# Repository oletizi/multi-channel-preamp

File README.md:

# Multi-Channel Preamp

## Description
Currently experimental KiCAD-based PCB project for a multi-channel vacuum tube preamp with insertable EQ.

## Layout
* `/src` where all the stuff is.
* `/src/schematics` where the KiCAD files live.
* `/src/schematics/build` where the KiCAD output files go. These are not under VC.
* `/src/schematics/610-output` example schematic from UA 610 preamp.
* `/src/gyraf-output` example preamp output stage from gyraf suitable for driving output transformer.
* `/src/multi-channel-preamp` schematics for the actual preamp.
* `/src/pmillett-output` example tube mic preamp schematic from pmillett.
* `/src/pultec-boost-high` prototype schematic & PCB for pultec-style high boost (from [Ian Thompson-Bell's Pultec 3 Band EQ](https://drive.google.com/drive/folders/0B_n67A1hN3qtfnhqS002NUo2WF9OTkZONDNqc3RBTS05SFlWLU4tbWItYVlZc01zejdrbGM?resourcekey=0-kD50Ger3JRaC0WO6iRfwKg)).
* `/src/pultec-cut-high` prototype schematic & PCB for pultec-style high cut (from [Ian Thompson-Bell's Pultec 3 Band EQ](https://drive.google.com/drive/folders/0B_n67A1hN3qtfnhqS002NUo2WF9OTkZONDNqc3RBTS05SFlWLU4tbWItYVlZc01zejdrbGM?resourcekey=0-kD50Ger3JRaC0WO6iRfwKg))
* `/src/pultec-three-band-eq` prototype schematic & PCB for full pultec-style 3-band eq (from [Ian Thompson-Bell's Pultec 3 Band EQ](https://drive.google.com/drive/folders/0B_n67A1hN3qtfnhqS002NUo2WF9OTkZONDNqc3RBTS05SFlWLU4tbWItYVlZc01zejdrbGM?resourcekey=0-kD50Ger3JRaC0WO6iRfwKg))

* `tapeop-output` example tube mic preamp schematic from TapeOp.

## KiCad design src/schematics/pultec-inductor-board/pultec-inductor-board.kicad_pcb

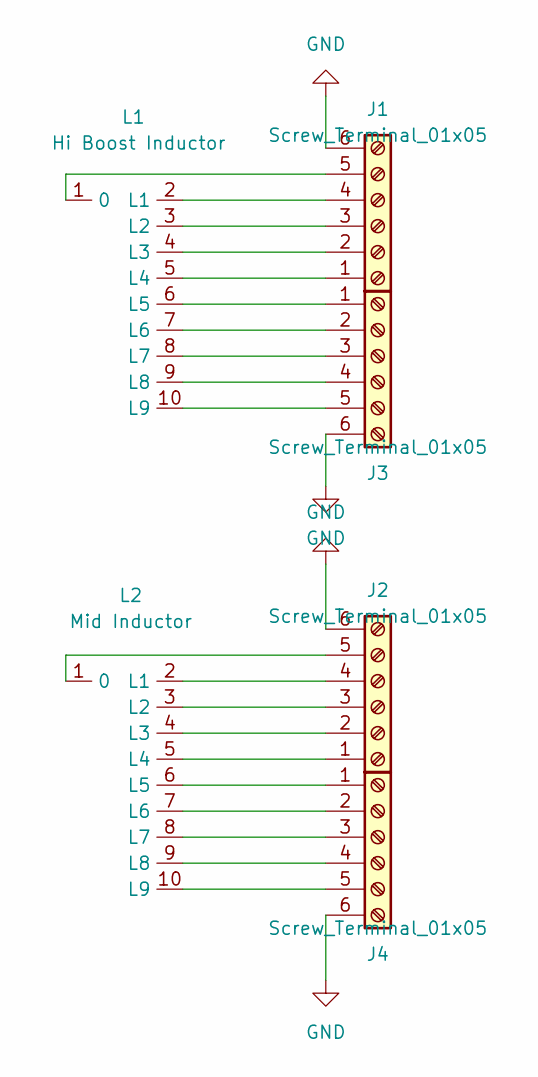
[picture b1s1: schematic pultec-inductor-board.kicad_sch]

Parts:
J1, J2, J3, J4: Screw_Terminal_01x05; TerminalBlock_Phoenix_MKDS-1,5-6_1x06_P5.00mm_Horizontal_Fa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
L1: Hi Boost Inductor; multi-inductor_EE16_10pin
L2: Mid Inductor; multi-inductor_EE16_10pin

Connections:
GND: J1.6, J2.6, J3.6, J4.6
unnamed: J1.1, L1.5 (L4)
unnamed: J1.2, L1.4 (L3)
unnamed: J1.3, L1.3 (L2)
unnamed: J1.4, L1.2 (L1)
unnamed: J1.5, L1.1 (0)
unnamed: J2.1, L2.5 (L4)
unnamed: J2.2, L2.4 (L3)
unnamed: J2.3, L2.3 (L2)
unnamed: J2.4, L2.2 (L1)
unnamed: J2.5, L2.1 (0)
unnamed: J3.1, L1.6 (L5)
unnamed: J3.2, L1.7 (L6)
unnamed: J3.3, L1.8 (L7)
unnamed: J3.4, L1.9 (L8)
unnamed: J3.5, L1.10 (L9)
unnamed: J4.1, L2.6 (L5)
unnamed: J4.2, L2.7 (L6)
unnamed: J4.3, L2.8 (L7)
unnamed: J4.4, L2.9 (L8)
unnamed: J4.5, L2.10 (L9)

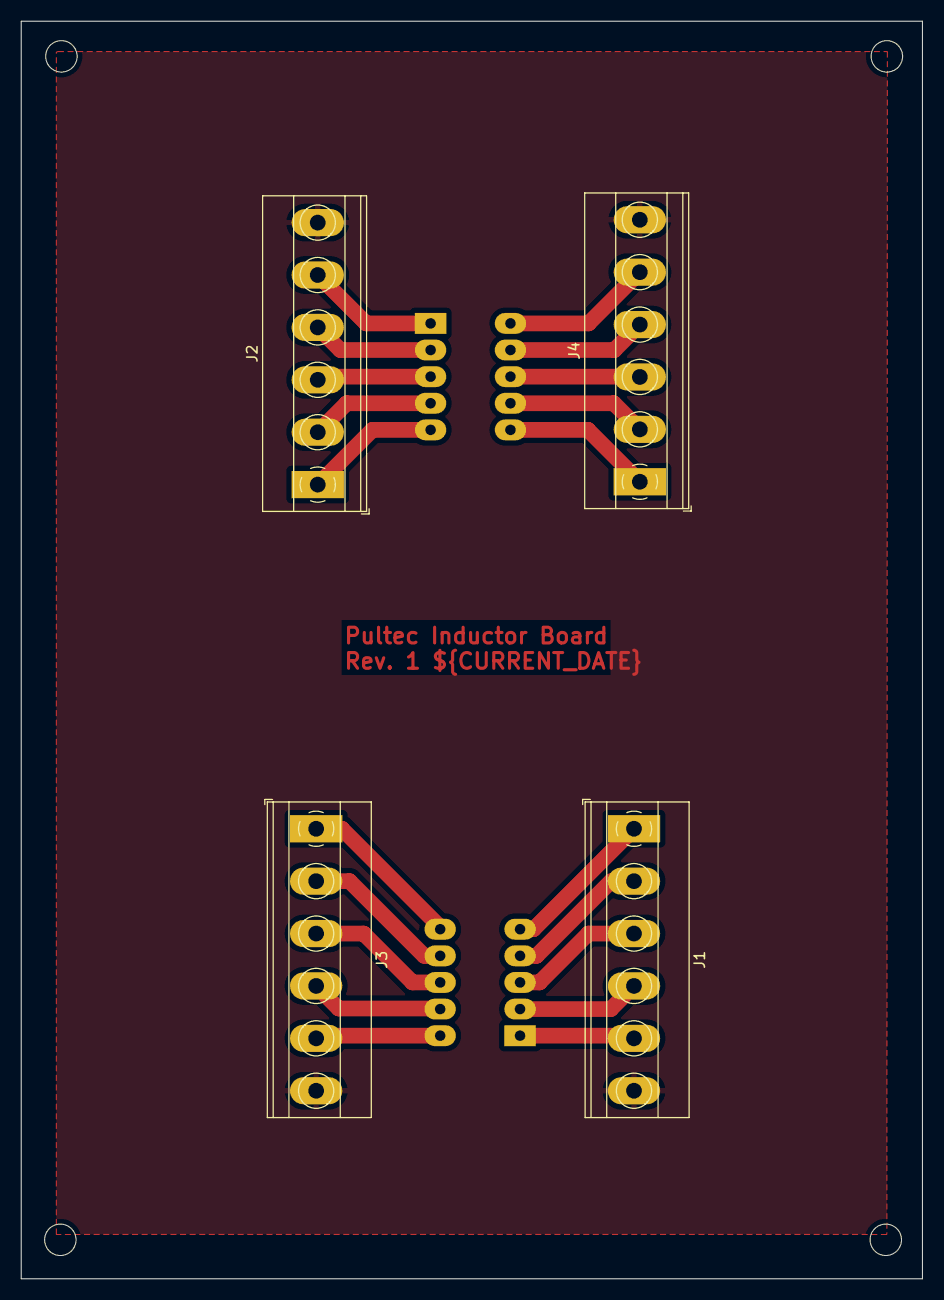
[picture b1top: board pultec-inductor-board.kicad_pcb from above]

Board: 2 copper layers, 86.0 x 120.0 mm, 6 parts (0 on the bottom side), 21 nets.

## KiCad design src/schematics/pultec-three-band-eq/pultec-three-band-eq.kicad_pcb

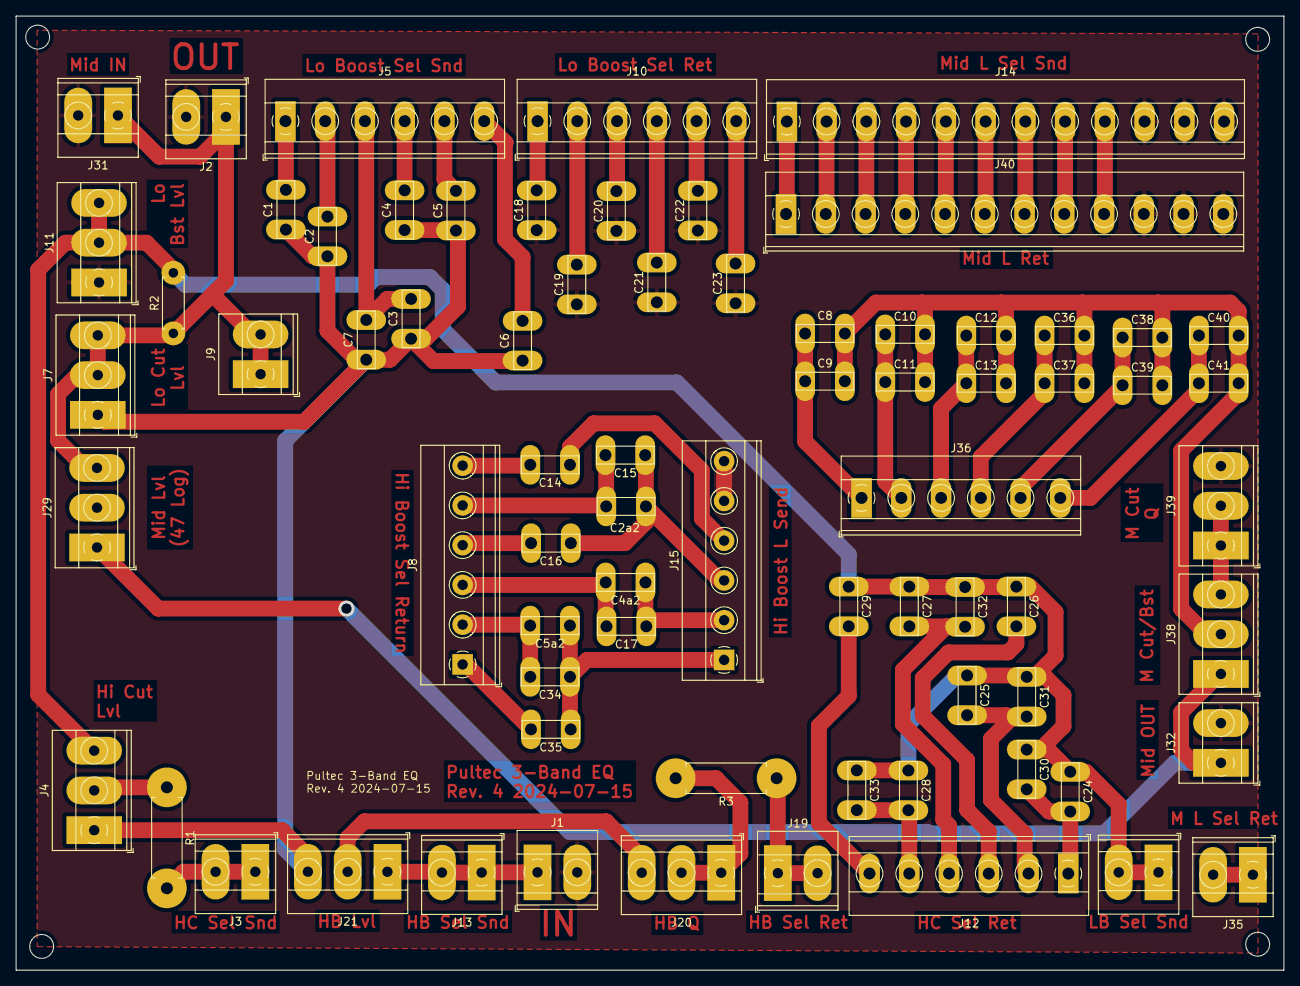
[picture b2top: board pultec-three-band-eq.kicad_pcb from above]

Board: 2 copper layers, 159.5 x 120.0 mm, 73 parts (0 on the bottom side), 57 nets.

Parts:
C1: 18n; C_Rect_L7.0mm_W2.0mm_P5.00mm_Fat_Pad
C2, C31, C32: 10n; C_Rect_L7.0mm_W2.0mm_P5.00mm_Fat_Pad
C2a2: 470pF; C_Rect_L7.0mm_W2.0mm_P5.00mm_Fat_Pad
C3: 4.7n; C_Rect_L7.0mm_W2.0mm_P5.00mm_Fat_Pad
C4, C16: 3n3; C_Rect_L7.0mm_W2.0mm_P5.00mm_Fat_Pad
C4a2, C17, C34, C35: 1nF; C_Rect_L7.0mm_W2.0mm_P5.00mm_Fat_Pad
C5, C33: 2n2; C_Rect_L7.0mm_W2.0mm_P5.00mm_Fat_Pad
C5a2: 1n5; C_Rect_L7.0mm_W2.0mm_P5.00mm_Fat_Pad
C6: 1n8; C_Rect_L7.0mm_W2.0mm_P5.00mm_Fat_Pad
C7: 1n; C_Rect_L7.0mm_W2.0mm_P5.00mm_Fat_Pad
C8: Mid C1A; C_Rect_L7.0mm_W2.0mm_P5.00mm_Fat_Pad
C9: Mid C1B; C_Rect_L7.0mm_W2.0mm_P5.00mm_Fat_Pad
C10: Mid C2A; C_Rect_L7.0mm_W2.0mm_P5.00mm_Fat_Pad
C11: Mid C2B; C_Rect_L7.0mm_W2.0mm_P5.00mm_Fat_Pad
C12: Mid C3A; C_Rect_L7.0mm_W2.0mm_P5.00mm_Fat_Pad
C13: Mid C3B; C_Rect_L7.0mm_W2.0mm_P5.00mm_Fat_Pad
C14, C15: 4n7; C_Rect_L7.0mm_W2.0mm_P5.00mm_Fat_Pad
C18: 330n; C_Rect_L7.0mm_W2.0mm_P5.00mm_Fat_Pad
C19: 220n; C_Rect_L7.0mm_W2.0mm_P5.00mm_Fat_Pad
C20: 120n; C_Rect_L7.0mm_W2.0mm_P5.00mm_Fat_Pad
C21: 68n; C_Rect_L7.0mm_W2.0mm_P5.00mm_Fat_Pad
C22, C24, C25, C26: 47n; C_Rect_L7.0mm_W2.0mm_P5.00mm_Fat_Pad
C23, C30: 33n; C_Rect_L7.0mm_W2.0mm_P5.00mm_Fat_Pad
C27, C28: 22n; C_Rect_L7.0mm_W2.0mm_P5.00mm_Fat_Pad
C29: 15n; C_Rect_L7.0mm_W2.0mm_P5.00mm_Fat_Pad
C36: Mid C4A; C_Rect_L7.0mm_W2.0mm_P5.00mm_Fat_Pad
C37: Mid C4B; C_Rect_L7.0mm_W2.0mm_P5.00mm_Fat_Pad
C38: Mid C5A; C_Rect_L7.0mm_W2.0mm_P5.00mm_Fat_Pad
C39: Mid C5B; C_Rect_L7.0mm_W2.0mm_P5.00mm_Fat_Pad
C40: Mid C6A; C_Rect_L7.0mm_W2.0mm_P5.00mm_Fat_Pad
C41: Mid C6B; C_Rect_L7.0mm_W2.0mm_P5.00mm_Fat_Pad
J1: IN; TerminalBlock_Phoenix_MKDS-1,5-2_1x02_P5.00mm_Horizontal Fa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
J2: OUT; TerminalBlock_Phoenix_MKDS-1,5-2_1x02_P5.00mm_Horizontal Fa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
J3: Hi Cut Sel Snd; TerminalBlock_Phoenix_MKDS-1,5-2_1x02_P5.00mm_Horizontal Fa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
J4: Hi Cut Lvl; TerminalBlock_Phoenix_MKDS-1,5-3_1x03_P5.00mm_Horizontal Fa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
J5: Lo Cut Sel Snd; TerminalBlock_Phoenix_MKDS-1,5-6_1x06_P5.00mm_Horizontal_Fa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
J6: Lo Boost Sel Snd; TerminalBlock_Phoenix_MKDS-1,5-2_1x02_P5.00mm_Horizontal Fa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
J7: Low Cut Lvl; TerminalBlock_Phoenix_MKDS-1,5-3_1x03_P5.00mm_Horizontal Fa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
J8: Hi Boost Sel Rtn; TerminalBlock_Phoenix_MKDS-1,5-6_1x06_P5.00mm_Horizontal
J9: Low Cut Sel Ret; TerminalBlock_Phoenix_MKDS-1,5-2_1x02_P5.00mm_Horizontal Fa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
J10: Lo Boost Sel Ret; TerminalBlock_Phoenix_MKDS-1,5-6_1x06_P5.00mm_Horizontal_Fa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
J11: Lo Boost Lvl; TerminalBlock_Phoenix_MKDS-1,5-3_1x03_P5.00mm_Horizontal Fa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
J12: Hi Cut Sel Ret; TerminalBlock_Phoenix_MKDS-1,5-6_1x06_P5.00mm_Horizontal_Fa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
J13: Hi Boost Sel Snd; TerminalBlock_Phoenix_MKDS-1,5-2_1x02_P5.00mm_Horizontal Fa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
J14: Mid L Sel send; TerminalBlock_Phoenix_MKDS-1,5-12_1x12_P5.00mm_Horizontal_F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
J15: Hi Boost L Snd; TerminalBlock_Phoenix_MKDS-1,5-6_1x06_P5.00mm_Horizontal
J19: Hi Boost Sel Ret; TerminalBlock_Phoenix_MKDS-1,5-2_1x02_P5.00mm_Horizontal Fa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
J20: Hi Boost Q; TerminalBlock_Phoenix_MKDS-1,5-3_1x03_P5.00mm_Horizontal Fa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
J21: Hi Boost Lvl; TerminalBlock_Phoenix_MKDS-1,5-3_1x03_P5.00mm_Horizontal Fa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
J29: Mid Lvl (47 Log); TerminalBlock_Phoenix_MKDS-1,5-3_1x03_P5.00mm_Horizontal Fa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
J31: Mid In; TerminalBlock_Phoenix_MKDS-1,5-2_1x02_P5.00mm_Horizontal Fa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
J32: Mid Out; TerminalBlock_Phoenix_MKDS-1,5-2_1x02_P5.00mm_Horizontal Fa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
J35: Mid L Sel Ret/C Sel Snd; TerminalBlock_Phoenix_MKDS-1,5-2_1x02_P5.00mm_Horizontal Fa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
J36: Mid C Sel Ret; TerminalBlock_Phoenix_MKDS-1,5-6_1x06_P5.00mm_Horizontal_Fa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
J38: Mid Cut/Bst Sw; TerminalBlock_Phoenix_MKDS-1,5-3_1x03_P5.00mm_Horizontal Fa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
J39: Mid Cut Q; TerminalBlock_Phoenix_MKDS-1,5-3_1x03_P5.00mm_Horizontal Fa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
J40: Mid L Ret; TerminalBlock_Phoenix_MKDS-1,5-12_1x12_P5.00mm_Horizontal_F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
R1: 430R; R_Axial_DIN0411_L9.9mm_D3.6mm_P12.70mm_Horizontal Fat Pad
R2: 56K; R_Axial_DIN0207_L6.3mm_D2.5mm_P7.62mm_Horizontal
R3: 4K7; R_Axial_DIN0411_L9.9mm_D3.6mm_P12.70mm_Horizontal Fat Pad

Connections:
/HI BOOST OUT: C1.1, C2.1, C3.1, C4.1, C5.1, C6.1, C7.1, J4.1, J7.1, J21.3
/IN: J1.1, J13.1, J13.2, J21.1
/LO BOOST IN: C24.1, C25.1, C26.1, C27.1, C28.1, C29.1, C30.1, C31.1, C32.1, C33.1, J4.3, J6.1, J6.2, J11.2, J11.3, R2.2
/OUT: J2.1, J7.2, J7.3, J9.1, J9.2, J29.3, J31.1, R2.1
/pultec-mid-band/MID OUT: J29.1, J32.1, J38.1
GND: C18.1, C19.1, C20.1, C21.1, C22.1, C23.1, J1.2, J2.2, J11.1, J14.10, J14.11, J14.12, J15.5, J15.6, J31.2, J32.2, J39.3, J40.10, J40.11, J40.12
unnamed: J3.1, J3.2, R1.2
unnamed: J4.2, R1.1
unnamed: C1.2, J5.1
unnamed: C2.2, J5.2
unnamed: C3.2, C7.2, J5.3
unnamed: C4.2, J5.4
unnamed: C5.2, J5.5
unnamed: C6.2, J5.6
unnamed: C35.2, J8.1
unnamed: C5a2.2, C34.2, J8.2
unnamed: C4a2.2, C17.2, J8.3
unnamed: C16.2, J8.4
unnamed: C2a2.2, C15.2, J8.5
unnamed: C14.2, J8.6
unnamed: C18.2, J10.1
unnamed: C19.2, J10.2
unnamed: C20.2, J10.3
unnamed: C21.2, J10.4
unnamed: C22.2, J10.5
unnamed: C23.2, J10.6
unnamed: C24.2, C30.2, J12.1
unnamed: C25.2, C31.2, J12.2
unnamed: C26.2, J12.3
unnamed: C27.2, C32.2, J12.4
unnamed: C28.2, C33.2, J12.5
unnamed: C29.2, J12.6
unnamed: J14.1, J40.1
unnamed: J14.2, J40.2
unnamed: J14.3, J40.3
unnamed: J14.4, J40.4
unnamed: J14.5, J40.5
unnamed: J14.6, J40.6
unnamed: J14.7, J40.7
unnamed: J14.8, J40.8
unnamed: J14.9, J40.9
unnamed: C5a2.1, C34.1, C35.1, J15.1
unnamed: C4a2.1, C17.1, J15.2
unnamed: C2a2.1, C15.1, C16.1, J15.3
unnamed: C14.1, J15.4
unnamed: J19.1, J19.2, R3.1
unnamed: J20.1, J20.2, R3.2
unnamed: J20.3, J21.2
unnamed: J35.1, J35.2
unnamed: C8.1, C9.1, J36.1
unnamed: C10.1, C11.1, J36.2
unnamed: C12.1, C13.1, J36.3
unnamed: C36.1, C37.1, J36.4
unnamed: C38.1, C39.1, J36.5
unnamed: C40.1, C41.1, J36.6
unnamed: C8.2, C9.2, C10.2, C11.2, C12.2, C13.2, C36.2, C37.2, C38.2, C39.2, C40.2, C41.2, J38.2
unnamed: J38.3, J39.1, J39.2

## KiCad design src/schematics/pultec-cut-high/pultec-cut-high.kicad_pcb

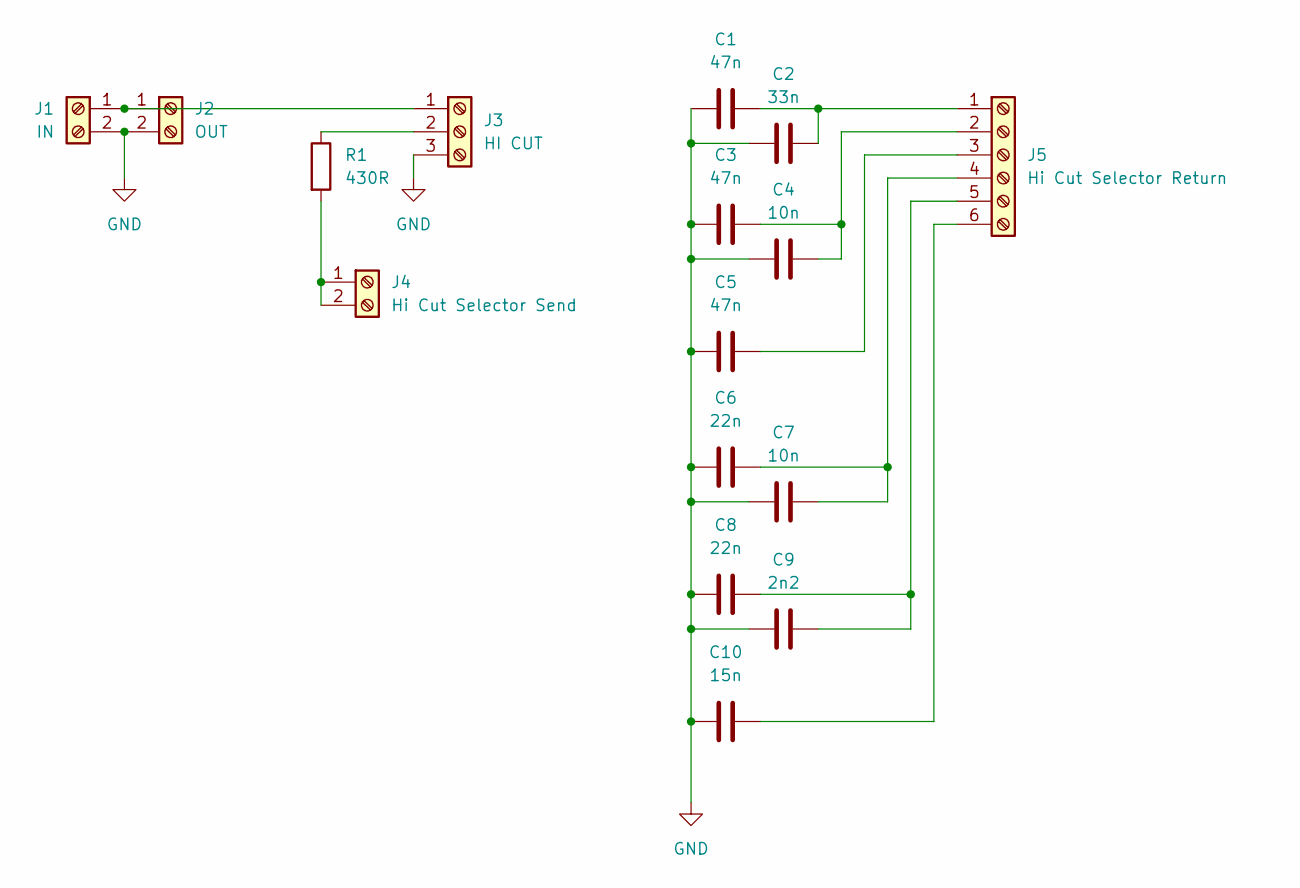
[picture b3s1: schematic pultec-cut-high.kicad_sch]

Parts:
C1, C3, C5: 47n; C_Rect_L7.0mm_W2.0mm_P5.00mm_Fat_Pad
C2: 33n; C_Rect_L7.0mm_W2.0mm_P5.00mm_Fat_Pad
C4, C7: 10n; C_Rect_L7.0mm_W2.0mm_P5.00mm_Fat_Pad
C6, C8: 22n; C_Rect_L7.0mm_W2.0mm_P5.00mm_Fat_Pad
C9: 2n2; C_Rect_L7.0mm_W2.0mm_P5.00mm_Fat_Pad
C10: 15n; C_Rect_L7.0mm_W2.0mm_P5.00mm_Fat_Pad
J1: IN; TerminalBlock_Phoenix_MKDS-1,5-2_1x02_P5.00mm_Horizontal Fa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
J2: OUT; TerminalBlock_Phoenix_MKDS-1,5-2_1x02_P5.00mm_Horizontal Fa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
J3: HI CUT; TerminalBlock_Phoenix_MKDS-1,5-3_1x03_P5.00mm_Horizontal Fa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
J4: Hi Cut Selector Send; TerminalBlock_Phoenix_MKDS-1,5-2_1x02_P5.00mm_Horizontal Fa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
J5: Hi Cut Selector Return; TerminalBlock_Phoenix_MKDS-1,5-6_1x06_P5.00mm_Horizontal_Fa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
R1: 430R; R_Axial_DIN0411_L9.9mm_D3.6mm_P12.70mm_Horizontal Fat Pad

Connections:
GND: C1.1, C2.1, C3.1, C4.1, C5.1, C6.1, C7.1, C8.1, C9.1, C10.1, J1.2, J2.2, J3.3
unnamed: J1.1, J2.1, J3.1
unnamed: J3.2, R1.1
unnamed: J4.1, J4.2, R1.2
unnamed: C1.2, C2.2, J5.1
unnamed: C3.2, C4.2, J5.2
unnamed: C5.2, J5.3
unnamed: C6.2, C7.2, J5.4
unnamed: C8.2, C9.2, J5.5
unnamed: C10.2, J5.6

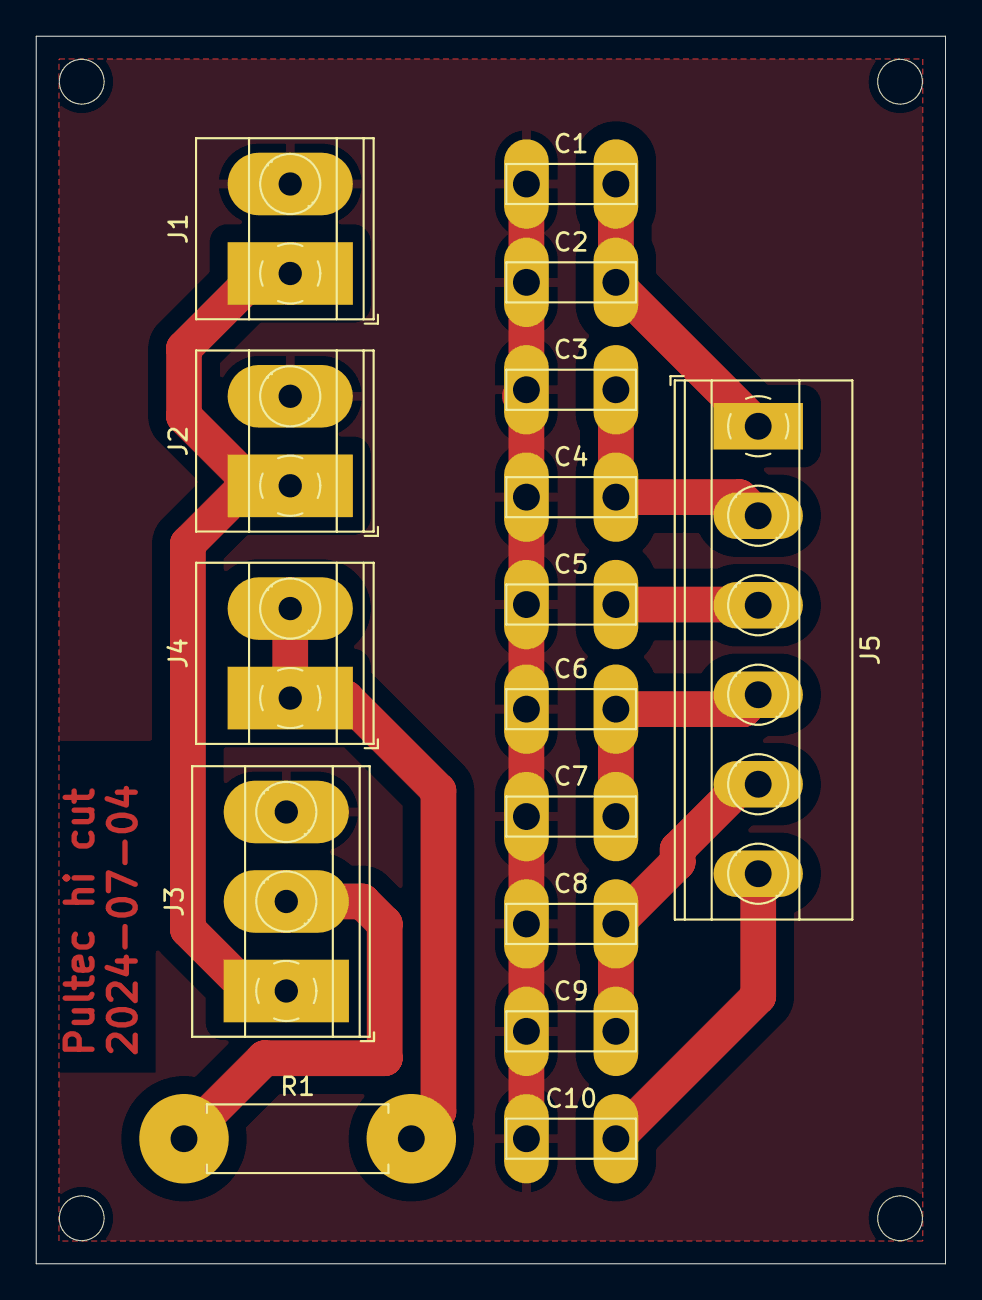
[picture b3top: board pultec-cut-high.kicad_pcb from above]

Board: 2 copper layers, 50.8 x 68.6 mm, 16 parts (0 on the bottom side), 10 nets.

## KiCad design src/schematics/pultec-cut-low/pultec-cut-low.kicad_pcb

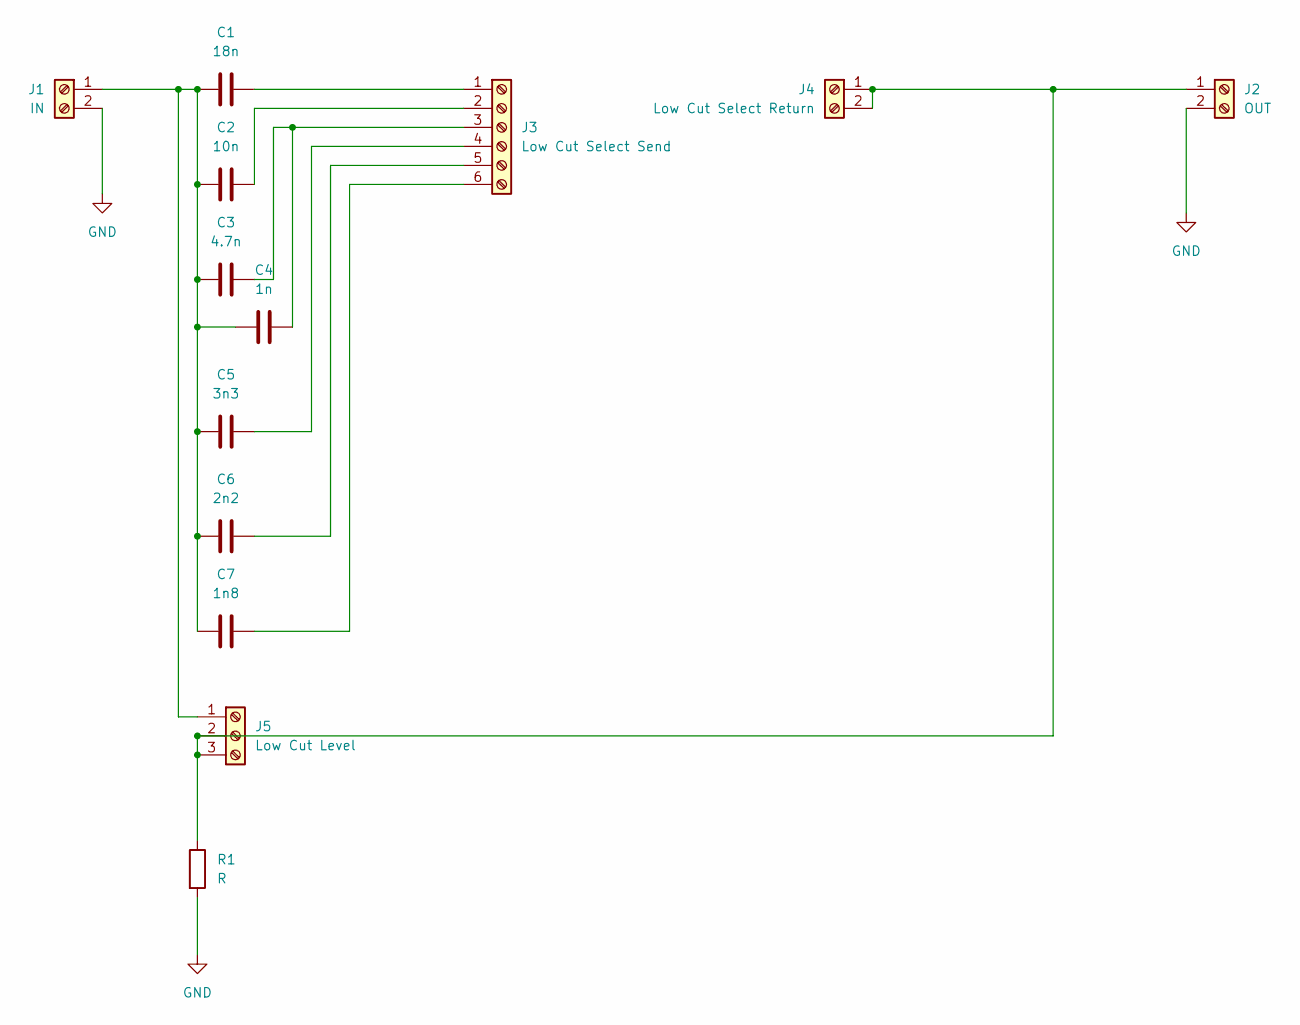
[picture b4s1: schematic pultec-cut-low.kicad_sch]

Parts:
C1: 18n; C_Rect_L7.0mm_W2.0mm_P5.00mm_Fat_Pad
C2: 10n; C_Rect_L7.0mm_W2.0mm_P5.00mm_Fat_Pad
C3: 4.7n; C_Rect_L7.0mm_W2.0mm_P5.00mm_Fat_Pad
C4: 1n; C_Rect_L7.0mm_W2.0mm_P5.00mm_Fat_Pad
C5: 3n3; C_Rect_L7.0mm_W2.0mm_P5.00mm_Fat_Pad
C6: 2n2; C_Rect_L7.0mm_W2.0mm_P5.00mm_Fat_Pad
C7: 1n8; C_Rect_L7.0mm_W2.0mm_P5.00mm_Fat_Pad
J1: IN; TerminalBlock_Phoenix_MKDS-1,5-2_1x02_P5.00mm_Horizontal Fa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
J2: OUT; TerminalBlock_Phoenix_MKDS-1,5-2_1x02_P5.00mm_Horizontal Fa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
J3: Low Cut Select Send; TerminalBlock_Phoenix_MKDS-1,5-6_1x06_P5.00mm_Horizontal_Fa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
J4: Low Cut Select Return; TerminalBlock_Phoenix_MKDS-1,5-2_1x02_P5.00mm_Horizontal Fa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
J5: Low Cut Level; TerminalBlock_Phoenix_MKDS-1,5-3_1x03_P5.00mm_Horizontal Fa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
R1: R; R_Axial_DIN0207_L6.3mm_D2.5mm_P7.62mm_Horizontal

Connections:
GND: J1.2, J2.2, R1.2
unnamed: C1.1, C2.1, C3.1, C4.1, C5.1, C6.1, C7.1, J1.1, J5.1
unnamed: J2.1, J4.1, J4.2, J5.2, J5.3, R1.1
unnamed: C1.2, J3.1
unnamed: C2.2, J3.2
unnamed: C3.2, C4.2, J3.3
unnamed: C5.2, J3.4
unnamed: C6.2, J3.5
unnamed: C7.2, J3.6

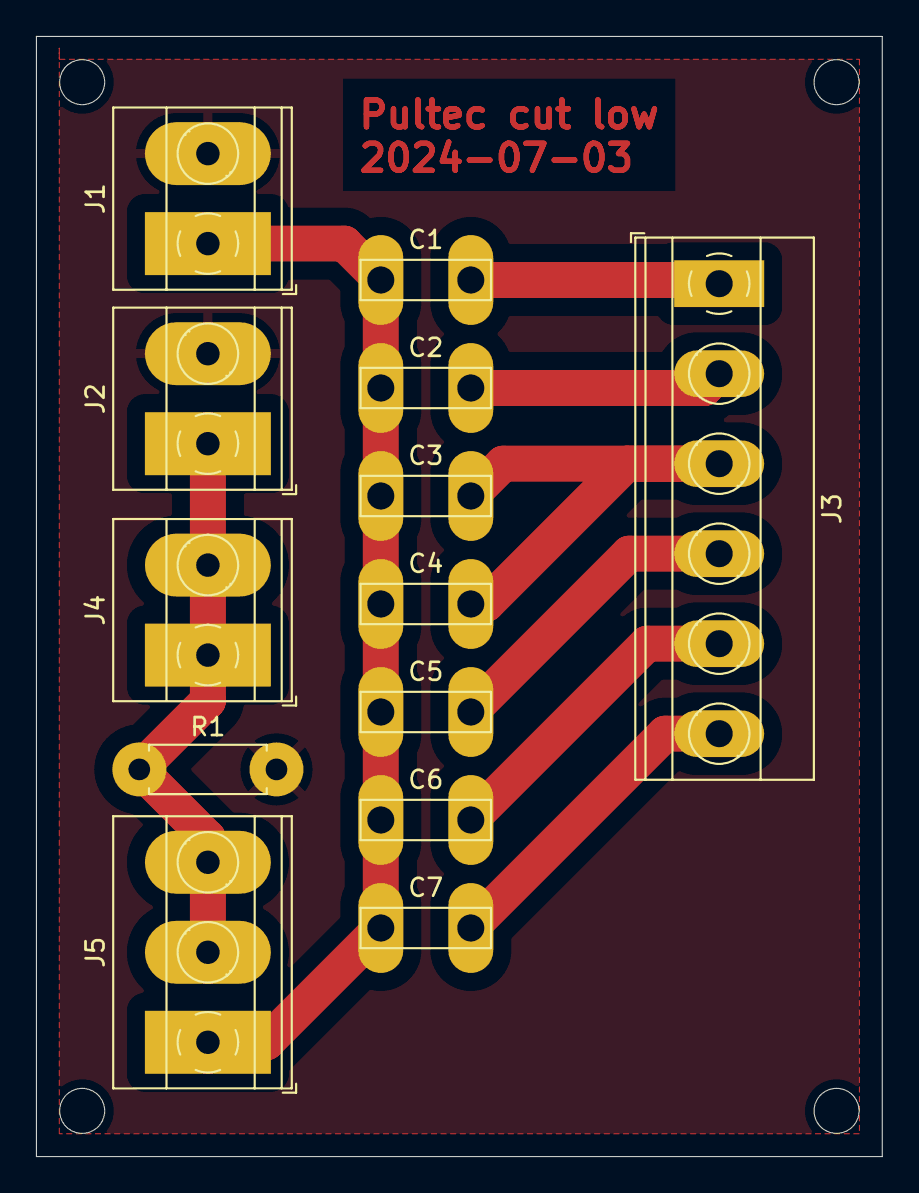
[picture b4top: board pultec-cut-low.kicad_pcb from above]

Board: 2 copper layers, 47.0 x 62.2 mm, 13 parts (0 on the bottom side), 9 nets.

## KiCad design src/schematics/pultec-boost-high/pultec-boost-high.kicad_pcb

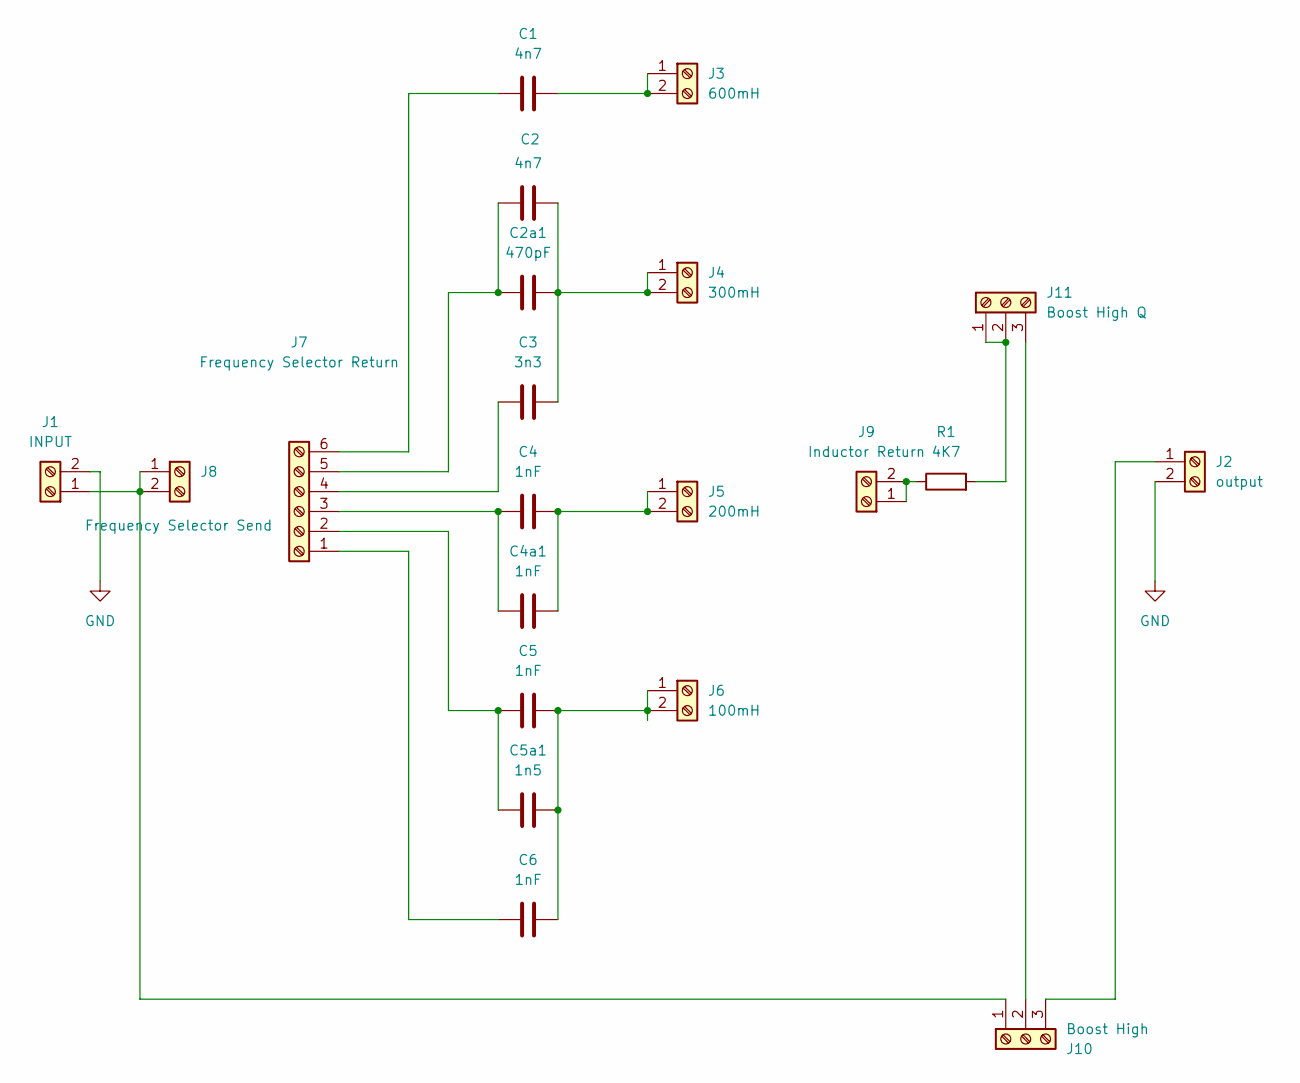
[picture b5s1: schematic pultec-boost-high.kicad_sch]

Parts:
C1, C2: 4n7; C_Rect_L7.0mm_W2.0mm_P5.00mm_Fat_Pad
C2a1: 470pF; C_Rect_L7.0mm_W2.0mm_P5.00mm_Fat_Pad
C3: 3n3; C_Rect_L7.0mm_W2.0mm_P5.00mm_Fat_Pad
C4, C4a1, C5, C6: 1nF; C_Rect_L7.0mm_W2.0mm_P5.00mm_Fat_Pad
C5a1: 1n5; C_Rect_L7.0mm_W2.0mm_P5.00mm_Fat_Pad
J1: INPUT; TerminalBlock_Phoenix_MKDS-1,5-2_1x02_P5.00mm_Horizontal Fa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
J2: output; TerminalBlock_Phoenix_MKDS-1,5-2_1x02_P5.00mm_Horizontal Fa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
J3: 600mH; TerminalBlock_Phoenix_MKDS-1,5-2_1x02_P5.00mm_Horizontal Fa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
J4: 300mH; TerminalBlock_Phoenix_MKDS-1,5-2_1x02_P5.00mm_Horizontal Fa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
J5: 200mH; TerminalBlock_Phoenix_MKDS-1,5-2_1x02_P5.00mm_Horizontal Fa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
J6: 100mH; TerminalBlock_Phoenix_MKDS-1,5-2_1x02_P5.00mm_Horizontal Fa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
J7: Frequency Selector Return; TerminalBlock_Phoenix_MKDS-1,5-6_1x06_P5.00mm_Horizontal
J8: Frequency Selector Send; TerminalBlock_Phoenix_MKDS-1,5-2_1x02_P5.00mm_Horizontal Fa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
J9: Inductor Return; TerminalBlock_Phoenix_MKDS-1,5-2_1x02_P5.00mm_Horizontal Fa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
J10: Boost High; TerminalBlock_Phoenix_MKDS-1,5-3_1x03_P5.00mm_Horizontal Fa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
J11: Boost High Q; TerminalBlock_Phoenix_MKDS-1,5-3_1x03_P5.00mm_Horizontal Fa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
R1: 4K7; R_Axial_DIN0411_L9.9mm_D3.6mm_P12.70mm_Horizontal Fat Pad

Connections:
GND: J1.2, J2.2
unnamed: J1.1, J8.1, J8.2, J10.1
unnamed: C1.2, J3.1, J3.2
unnamed: C2.2, C2a1.2, C3.2, J4.1, J4.2
unnamed: C4.2, C4a1.2, J5.1, J5.2
unnamed: C5.2, C5a1.2, C6.2, J6.1, J6.2
unnamed: C6.1, J7.1
unnamed: C5.1, C5a1.1, J7.2
unnamed: C4.1, C4a1.1, J7.3
unnamed: C3.1, J7.4
unnamed: C2.1, C2a1.1, J7.5
unnamed: C1.1, J7.6
unnamed: J9.1, J9.2, R1.1
unnamed: J10.2, J11.3
unnamed: J2.1, J10.3
unnamed: J11.1, J11.2, R1.2

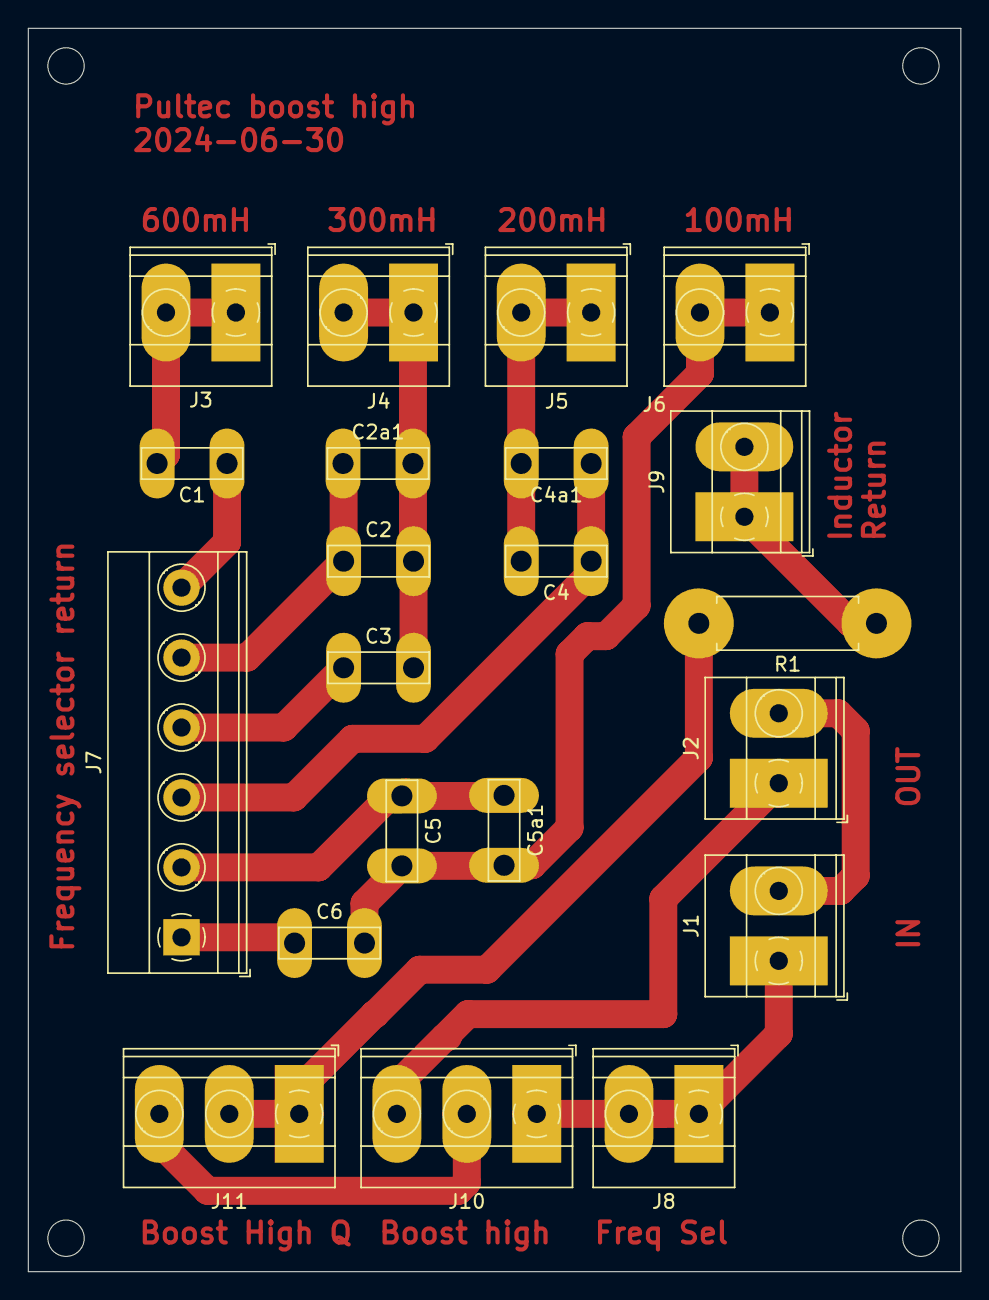
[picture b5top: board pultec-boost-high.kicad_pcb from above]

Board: 2 copper layers, 66.7 x 88.9 mm, 21 parts (0 on the bottom side), 16 nets.

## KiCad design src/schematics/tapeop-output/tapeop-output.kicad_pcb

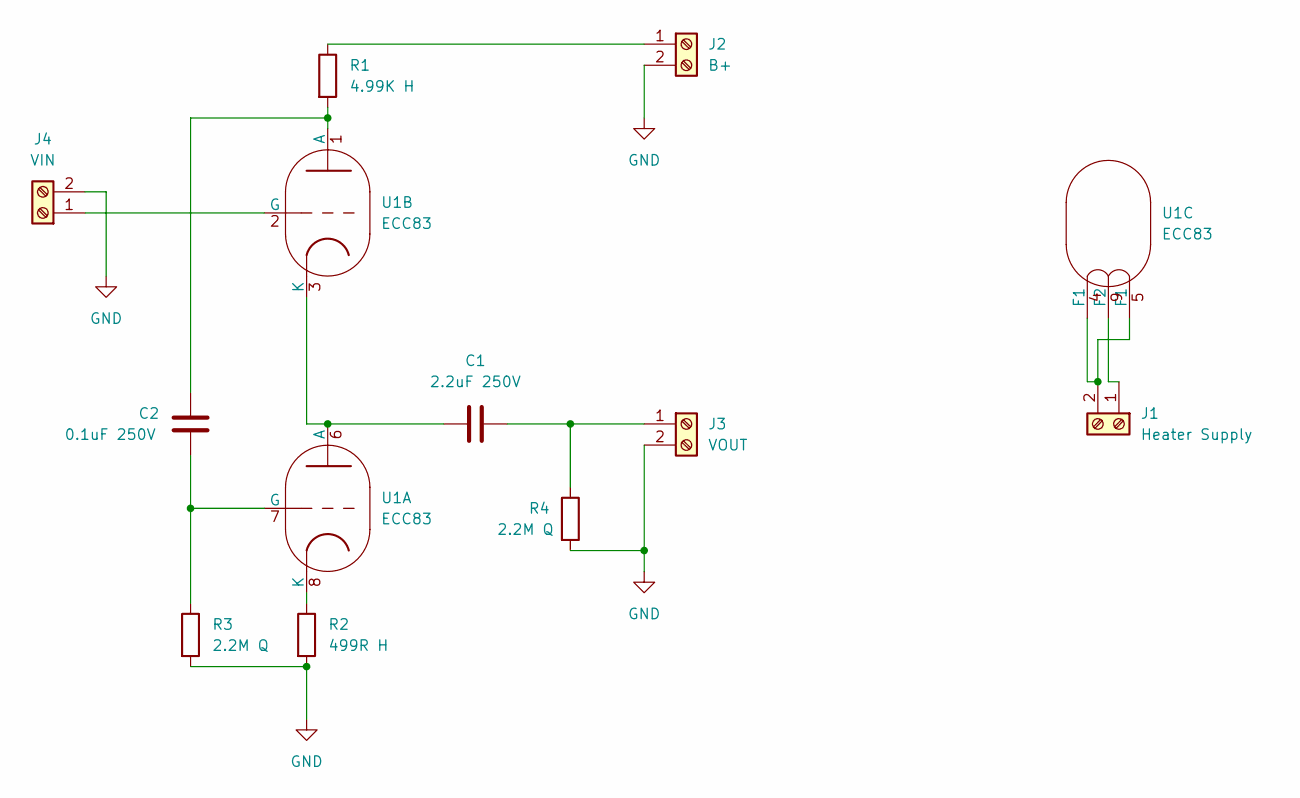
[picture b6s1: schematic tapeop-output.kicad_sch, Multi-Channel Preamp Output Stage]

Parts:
C1: 2.2uF 250V; C_Axial_L12.0mm_D8.5mm_P15.00mm_Horizontal Fat Pad
C2: 0.1uF 250V; C_Axial_L12.0mm_D8.5mm_P15.00mm_Horizontal Fat Pad
J1: Heater Supply; TerminalBlock_Phoenix_MKDS-1,5-2_1x02_P5.00mm_Horizontal Fa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
J2: B+; TerminalBlock_Phoenix_MKDS-1,5-2_1x02_P5.00mm_Horizontal Fa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
J3: VOUT; TerminalBlock_Phoenix_MKDS-1,5-2_1x02_P5.00mm_Horizontal Fa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
J4: VIN; TerminalBlock_Phoenix_MKDS-1,5-2_1x02_P5.00mm_Horizontal Fa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
R1: 4.99K H; R_Axial_DIN0411_L9.9mm_D3.6mm_P12.70mm_Horizontal Fat Pad
R2: 499R H; R_Axial_DIN0411_L9.9mm_D3.6mm_P12.70mm_Horizontal Fat Pad
R3, R4: 2.2M Q; R_Axial_DIN0411_L9.9mm_D3.6mm_P12.70mm_Horizontal Fat Pad
U1: ECC83; BELTON_VT9-PT Fat Pad

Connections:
GND: J2.2, J3.2, J4.2, R2.2, R3.2, R4.2
unnamed: J1.1, U1.9 (F2)
unnamed: J1.2, U1.4 (F1), U1.5 (F1)
unnamed: J2.1, R1.1
unnamed: C1.2, J3.1, R4.1
unnamed: J4.1, U1.2 (G)
unnamed: C1.1, U1.3 (K), U1.6 (A)
unnamed: C2.2, R3.1, U1.7 (G)
unnamed: R2.1, U1.8 (K)
unnamed: C2.1, R1.2, U1.1 (A)

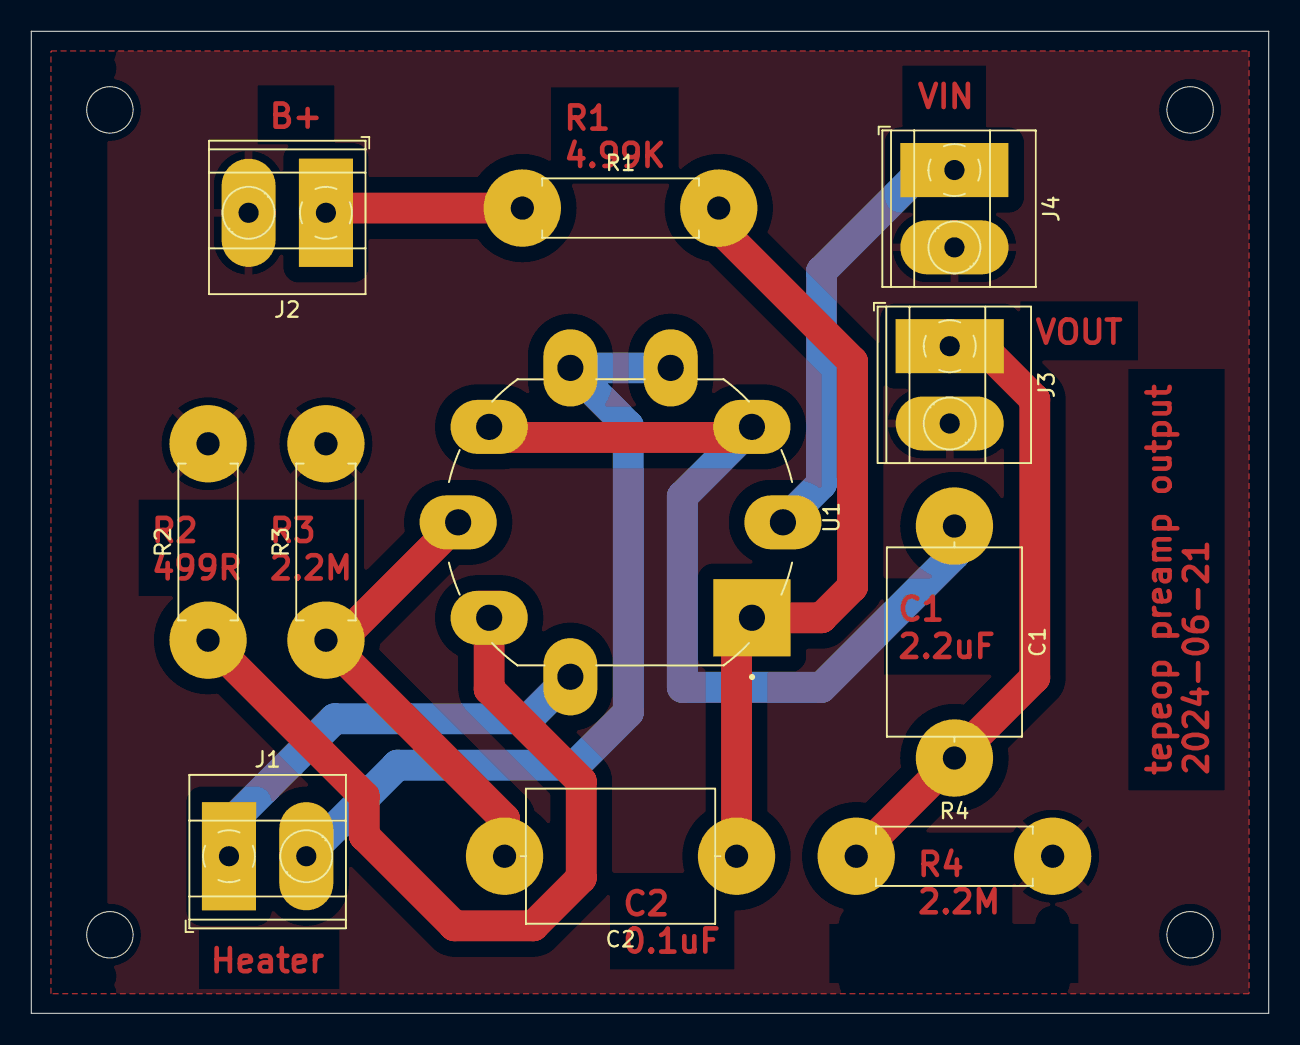
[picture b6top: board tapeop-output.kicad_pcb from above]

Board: 2 copper layers, 80.0 x 63.5 mm, 11 parts (0 on the bottom side), 10 nets.
